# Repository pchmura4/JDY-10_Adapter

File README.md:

# JDY-10_Adapter
Simple adapter for JDY-10 Bluetooth 4.0 module for prototyping purposes

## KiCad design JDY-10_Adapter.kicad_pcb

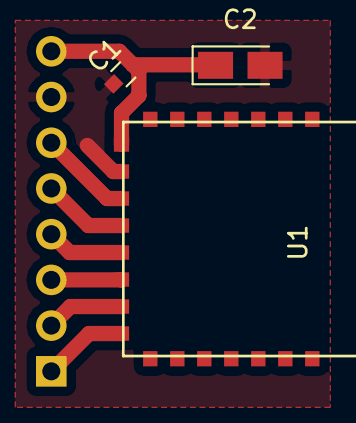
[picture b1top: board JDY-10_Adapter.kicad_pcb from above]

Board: 2 copper layers, 4 parts (1 on the bottom side), 8 nets.

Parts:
C1: C; C_0603
C2: CP; CP_Tantalum_Case-A_EIA-3216-18_Reflow
J1: CONN_01X08; Pin_Header_Straight_1x08_Pitch2.54mm
U1: JDY-10

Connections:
GND: C1.1, C2.2, J1.7, U1.9
unnamed: C1.2, C2.1, J1.8, U1.8
unnamed: J1.1, U1.15
unnamed: J1.2, U1.14
unnamed: J1.3, U1.13
unnamed: J1.4, U1.12
unnamed: J1.5, U1.11
unnamed: J1.6, U1.10
